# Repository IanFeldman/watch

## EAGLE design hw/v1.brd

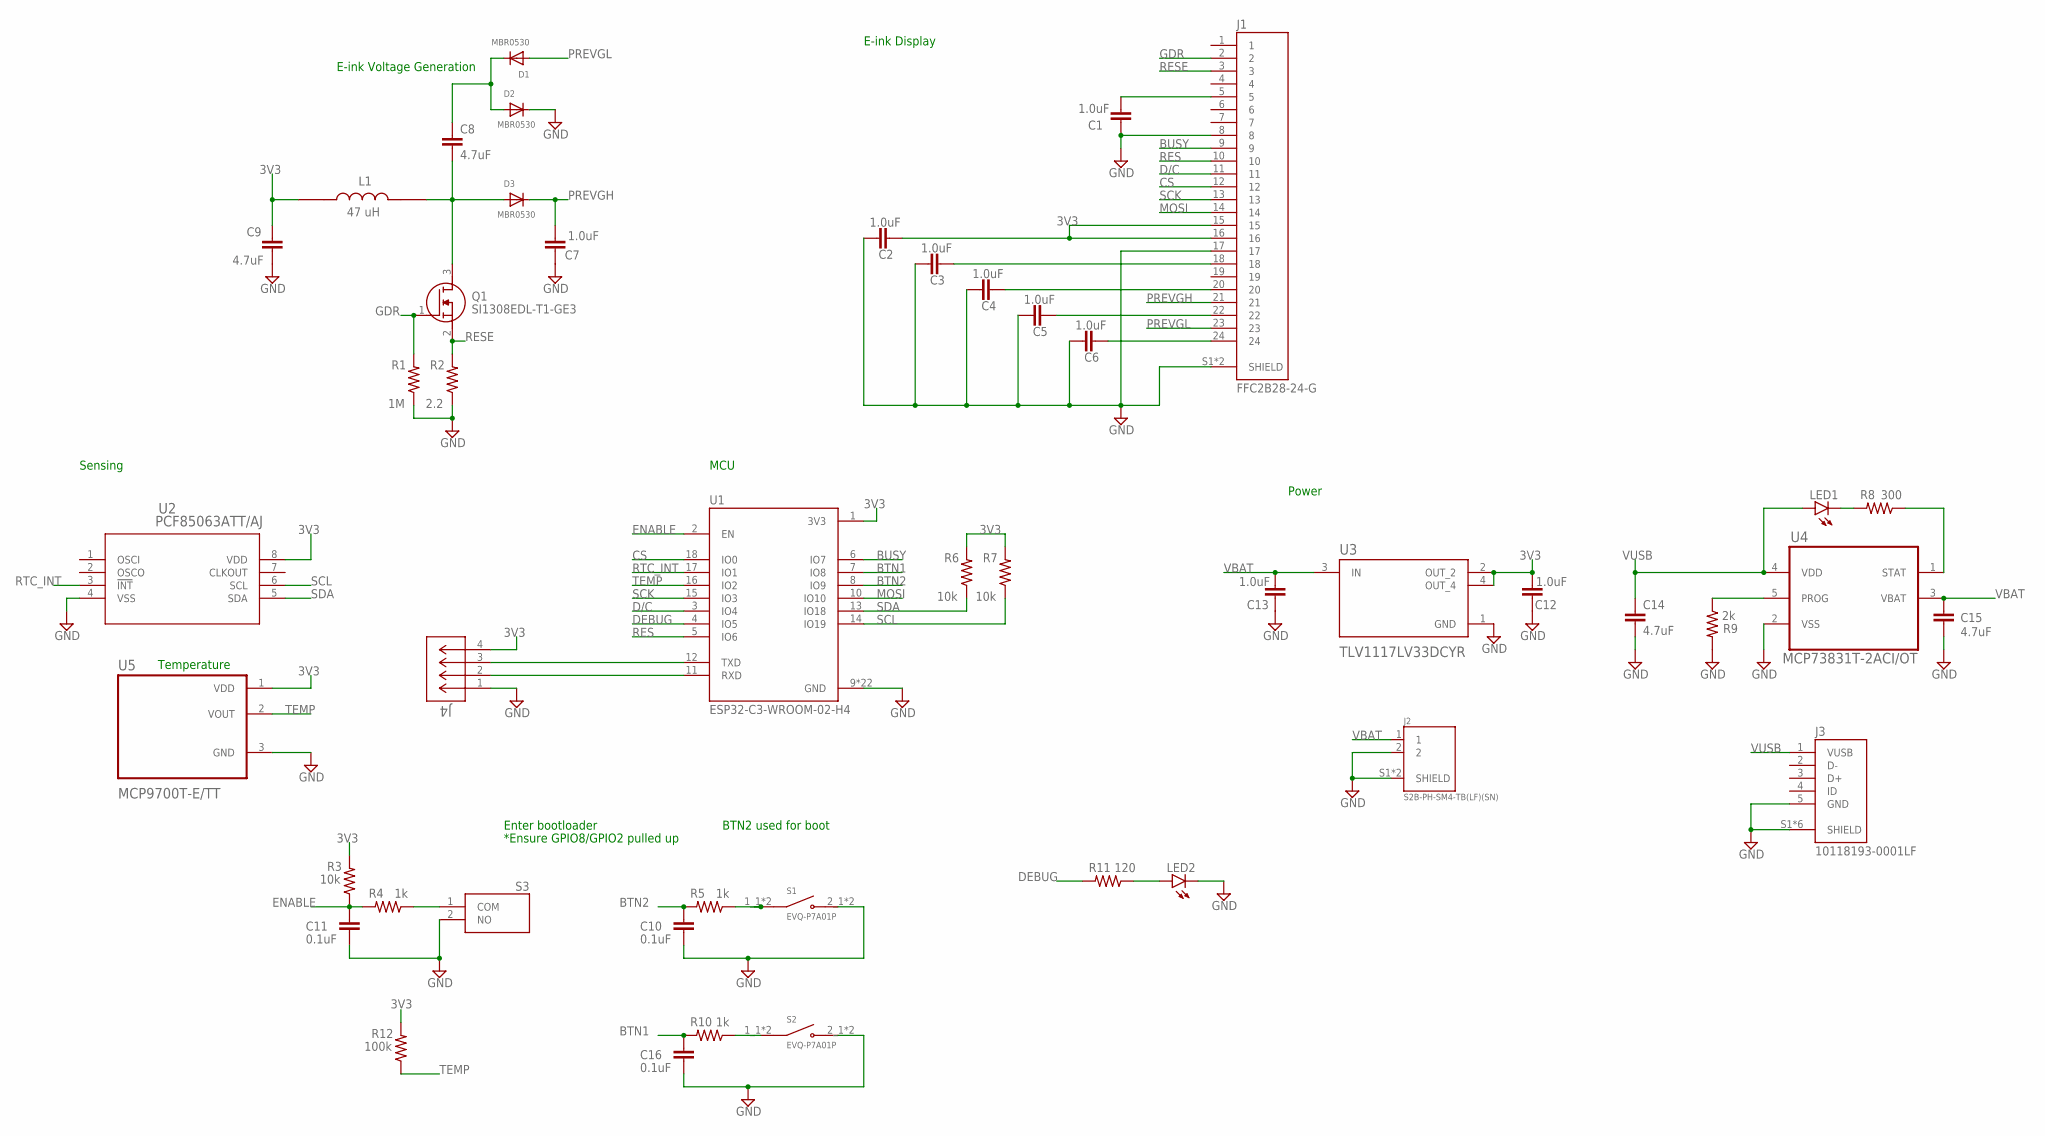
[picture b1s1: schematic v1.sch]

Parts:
C1, C2, C3, C4, C5, C6, C7, C12, C13: 1.0uF; 0603
C8, C9, C14, C15: 4.7uF; 0603
C10, C11, C16: 0.1uF; 0603
D1, D2, D3: MBR0530; SOD323F
J1: FFC2B28-24-G; GCT_FFC2B28-24-G
J2: S2B-PH-SM4-TB(LF)(SN); JST_S2B-PH-SM4-TB(LF)(SN)
J3: 10118193-0001LF; AMPHENOL_10118193-0001LF
J4: 851-43-004-20-001000; CONN_851-43-004-20-001000_MIM
L1: 47 uH; IND_ADL3225V-470MT-TL000
LED1, LED2: LEDCHIP-LED0603; CHIP-LED0603
Q1: SI1308EDL-T1-GE3; SOT65P210X110-3N
R1: 1M; R0603
R2: 2.2; R0603
R3, R6, R7: 10k; R0603
R4, R5, R10: 1k; R0603
R8: 300; R0603
R9: 2k; R0603
R11: 120; R0603
R12: 100k; R0603
S1, S2: EVQ-P7A01P; SW_EVQ-P7A01P
S3: PTS636_SM25F_SMTR_LFS; PTS636SM25FSMTRLFS
U1: ESP32-C3-WROOM-02-H4; MODULE_ESP32-C3-WROOM-02-H4
U2: PCF85063ATT/AJ; PCF85063ATT/AJ_NXP
U3: TLV1117LV33DCYR; VREG_TLV1117LV33DCYR
U4: MCP73831T-2ACI/OT; SOT95P280X145-5N
U5: MCP9700T-E/TT; SOT95P237X112-3N

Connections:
3V3: C2.1, C9.1, C12.1, J1.15, J1.16, J4.4, L1.1, R3.2, R6.2, R7.2, R12.2, U1.1 (3V3), U2.8 (VDD), U3.2 (OUT_2), U3.4 (OUT_4), U5.1 (VDD)
BTN1: C16.1, R10.2, U1.7 (IO8)
BTN2: C10.1, R5.2, U1.8 (IO9)
BUSY: J1.9, U1.6 (IO7)
CS: J1.12, U1.18 (IO0)
D/C: J1.11, U1.3 (IO4)
DEBUG: R11.2, U1.4 (IO5)
ENABLE: C11.1, R3.1, R4.2, U1.2 (EN)
GDR: J1.2, Q1.1 (G), R1.2
GND: C1.2, C2.2, C3.2, C4.2, C5.2, C6.2, C7.2, C9.2, C10.2, C11.2, C12.2, C13.2, C14.2, C15.2, C16.2, D2.C, J1.8, J1.17, J1.S1 (SHIELD), J1.S2 (SHIELD), J2.2, J2.S1 (SHIELD), J2.S2 (SHIELD), J3.5 (GND), J3.S1 (SHIELD), J3.S2 (SHIELD), J3.S3 (SHIELD), J3.S4 (SHIELD), J3.S5 (SHIELD), J3.S6 (SHIELD), J4.1, LED2.C, R1.1, R2.1, R9.2, S1.2_1 (2), S1.2_2 (2), S2.2_1 (2), S2.2_2 (2), S3.2 (NO), U1.9 (GND), U1.19 (GND), U1.20 (GND), U1.21 (GND), U1.22 (GND), U1.23 (GND), U1.24 (GND), U1.25 (GND), U1.26 (GND), U1.27 (GND), U1.28 (GND), U1.29 (GND), U1.30 (GND), U1.31 (GND), U1.32 (GND), U1.33 (GND), U1.34 (GND), U1.35 (GND), U1.36 (GND), U1.37 (GND), U1.38 (GND), U1.39 (GND), U2.4 (VSS), U3.1 (GND), U4.2 (VSS), U5.3 (GND)
MOSI: J1.14, U1.10 (IO10)
unnamed: C1.1, J1.5
unnamed: C3.1, J1.18
unnamed: C4.1, J1.20
unnamed: C5.1, J1.22
unnamed: C8.2, D3.A, L1.2, Q1.3 (D)
unnamed: C6.1, J1.24
unnamed: C8.1, D1.C, D2.A
unnamed: R4.1, S3.1 (COM)
unnamed: R5.1, S1.1_1 (1), S1.1_2 (1)
unnamed: R10.1, S2.1_1 (1), S2.1_2 (1)
unnamed: J4.3, U1.12 (TXD)
unnamed: J4.2, U1.11 (RXD)
unnamed: LED1.C, R8.2
unnamed: R8.1, U4.1 (STAT)
unnamed: R9.1, U4.5 (PROG)
unnamed: LED2.A, R11.1
PREVGH: C7.1, D3.C, J1.21
PREVGL: D1.A, J1.23
RES: J1.10, U1.5 (IO6)
RESE: J1.3, Q1.2 (S), R2.2
RTC_INT: U1.17 (IO1), U2.3 (!INT)
SCK: J1.13, U1.15 (IO3)
SCL: R7.1, U1.14 (IO19), U2.6 (SCL)
SDA: R6.1, U1.13 (IO18), U2.5 (SDA)
TEMP: R12.1, U1.16 (IO2), U5.2 (VOUT)
VBAT: C13.1, C15.1, J2.1, U3.3 (IN), U4.3 (VBAT)
VUSB: C14.1, J3.1 (VUSB), LED1.A, U4.4 (VDD)

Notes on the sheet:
E-ink Voltage Generation
Enter bootloader
*Ensure GPIO8/GPIO2 pulled up
Power
Sensing
MCU
E-ink Display
BTN2 used for boot
Temperature

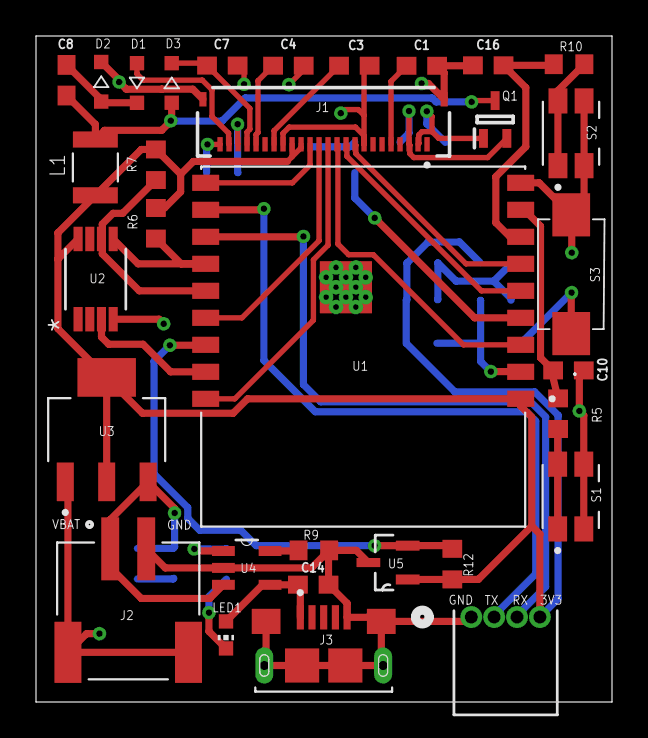
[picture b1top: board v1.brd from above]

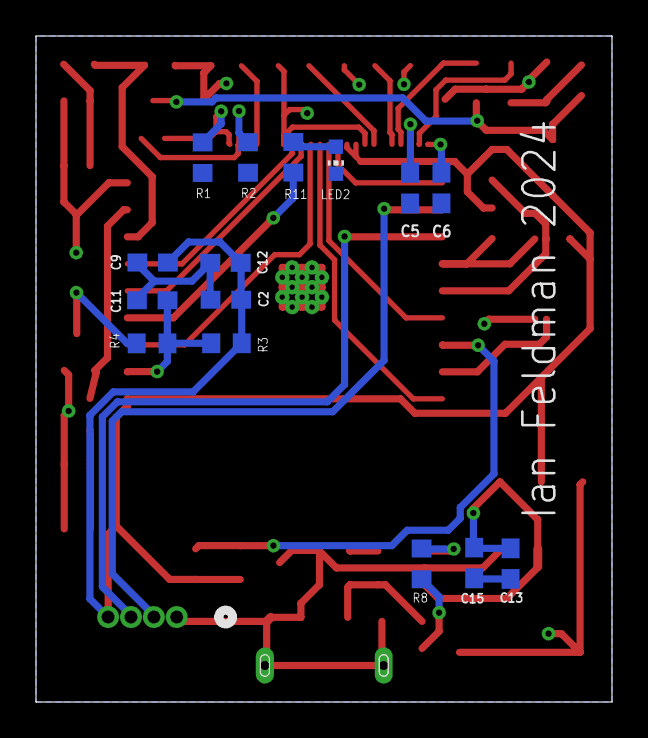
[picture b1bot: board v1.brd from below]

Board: 2 copper layers, 32.0 x 37.0 mm, 47 parts (15 on the bottom side), 38 nets.

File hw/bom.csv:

Part,Details,Symbol,Price,Quantity,Part Number
esp32-c3,wroom-02,U1,1.9,1,1965-ESP32-C3-WROOM-02-N4CT-ND
e-ink,"200x200, bw, 1.54in",,7.2,1,2544-AES200200A00-1.54ENRS-ND
ffc connector,"24-pos, 0.5mm pitch",J1,0.67,1,2073-FFC2B28-24-GCT-ND
1uf/25v cap,series 0603,"C1...C7, C12, C13",0.1,9,1276-1184-1-ND
4.7uf/25v cap,series 0603,"C8, C9, C14, C15",0.1,4,1276-1044-1-ND
0.1uf cap,series 0603,"C10, C11, C16",0.1,2,1276-1000-1-ND
schottky diode,30V 500mA,D1...D3,0.21,3,MBR0530TPMSCT-ND
inductor,"47uH, 570mA",L1,1.17,1,445-174611-1-ND
nmos,,Q1,0.44,1,SI1308EDL-T1-GE3CT-ND
resistor 1M,series 0603,R1,0.1,1,CR0603-FX-1004ELFCT-ND
resistor 2.2,series 0603,R2,0.1,1,CR0603-J/-2R2ELFCT-ND
resistor 10k,series 0603,"R3, R6, R7",0.1,3,CR0603-FX-1002ELF
resistor 1k,series 0603,"R4, R5, R10",0.1,3,CR0603-JW-102ELFCT-ND
resistor 300,series 0603,R8,0.1,1,118-CR0603-FX-3000ELFCT-ND
resistor 2k,series 0603,R9,0.1,1,CR0603-FX-2001ELFCT-ND
resistor 120,series 0603,R11,0.1,1,CR0603-FX-1200ELFCT-ND
resistor 100k,series 0603,R12,0.1,1,CR0603-FX-1003ELFCT-ND
push button,"mom, no",S3,0.24,1,CKN12330-1-ND
uart connector,"4-pos, 0.05in pitch",J4,2.53,1,ED90474-ND
rtc,i2c,U2,1.49,1,568-12404-1-ND
linear regulator,3.3v,U3,0.35,1,296-28778-1-ND
battery,"3.7V, 500mAh",,7.95,1,1528-1841-ND
jst ph connector,,J2,0.58,1,455-S2B-PH-SM4-TBCT-ND
usb connector,micro,J3,0.57,1,609-4616-1-ND
charger,,U4,0.76,1,MCP73831T-2ACI/OTCT-ND
led,series 0603,"LED1, LED2",0.21,2,160-1183-1-ND
side button,"mom, no","S1, S2",0.29,2,P16763CT-ND
temperature sensor,analog,U5,0.3,1,MCP9700T-E/TTCT-ND

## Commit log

2024-08-20 Init commit
2024-08-20 Create display driver
2024-08-23 Add schematic, bill of materials
2024-08-24 Add boot buttons, rtc, ldo
2024-08-25 Add charging hardware, change buttons
2024-08-25 Add usb to bom
2024-08-25 Add board
2024-08-25 Finish basic board layout, change reset button
2024-08-26 Add temperature sensor
2024-08-26 Change inductor, add part numbers to bom
2024-08-27 Find passive parts, change led resistor to 300 ohm
2024-08-27 Hw changes
2024-08-28 Add text to board
2024-08-28 Remove unnecessary text
2024-08-28 Minor changes
2024-08-28 Change esp32
2024-08-29 Add schematic image
2024-08-29 Refactor display driver, style changes
2024-08-31 Add ability to write images, clear screen, font files, conditional compilation flag for development
2024-08-31 Added to font, changed screen clear to ram clear
2024-09-06 Scale images, change font to array, create util
2024-09-06 Change image_t to have only width, height, and data
2024-09-11 Put font images in array, fix write_to_ram bugs, add bit offset to bitwise scale
2024-09-12 Rework bitwise scale function
2024-09-12 Update font letters
2024-09-18 Create write string function

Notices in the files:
parts and their libraries:
SparkFun-Capacitors: Licensing: Creative Commons ShareAlike 4.0 International - https://creativecommons.org/licenses/by-sa/4.0
COPYRIGHT: Copyright (C) 2024 Ultra Librarian. All rights reserved.
